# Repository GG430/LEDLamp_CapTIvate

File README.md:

View this project on [CADLAB.io](https://cadlab.io/project/1076). 

# LEDLamp_CapTIvate

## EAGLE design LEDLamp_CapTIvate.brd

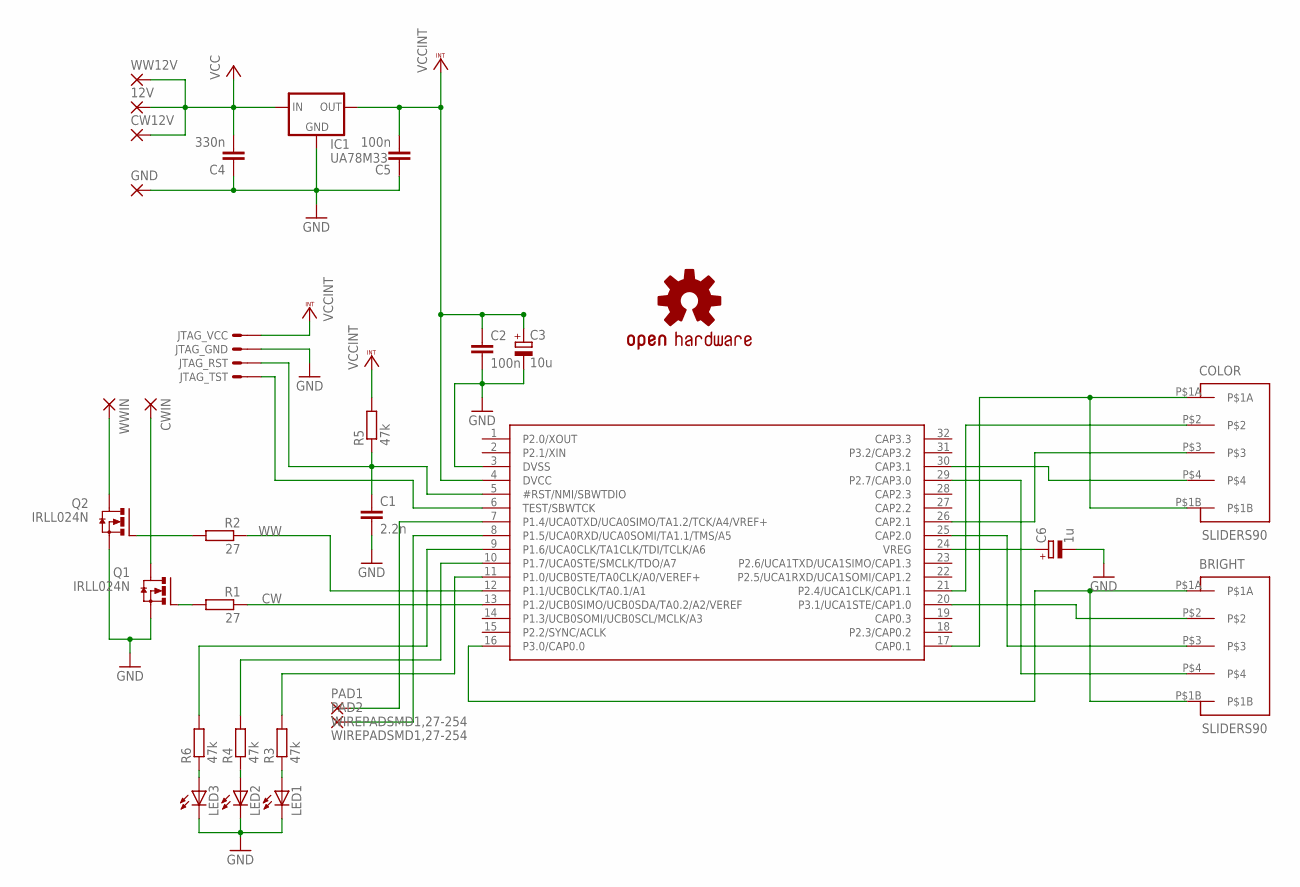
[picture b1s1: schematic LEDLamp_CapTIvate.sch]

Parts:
12V: SMD5; SMD2,54-5,08
BRIGHT: SLIDERS90; SLIDER90
C1: 2.2n; C0805
C2, C5: 100n; C0805
C3: 10u; R/2012-12R
C4: 330n; C0805
C6: 1u; R/2012-12R
COLOR: SLIDERS90; SLIDER90
CW12V: SMD5; SMD2,54-5,08
CWIN: SMD5; SMD2,54-5,08
GND: SMD5; SMD2,54-5,08
IC1: UA78M33; SOT223
JTAG_: MSP430SBWMPE; MPE-374-04
LED1, LED2, LED3: LEDTOPLED-SANTANA; MINI-TOPLED-SANTANA
MSP430FR2633: FR2633; DA32
PAD1, PAD2: WIREPADSMD1,27-254; SMD3X1.5
Q1, Q2: IRLL024N; SOT223
R1, R2: 27; R0805
R3, R4, R5, R6: 47k; R0805
U$2: OSHW_LOGO_SYMM; OSHW_LOGO_MED_SYM
WW12V: SMD5; SMD2,54-5,08
WWIN: SMD5; SMD2,54-5,08

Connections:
CW: MSP430FR2633.13 (P1.2/UCB0SIMO/UCB0SDA/TA0.2/A2/VEREF), R1.1
GND: C1.2, C2.2, C3.-, C4.1, C5.1, C6.-, GND.1, IC1.2 (GND), JTAG_.P$2, LED1.C, LED2.C, LED3.C, MSP430FR2633.3 (DVSS), Q1.3 (S), Q2.3 (S)
unnamed: BRIGHT.P$1A, BRIGHT.P$1B, MSP430FR2633.16 (P3.0/CAP0.0)
unnamed: BRIGHT.P$2, MSP430FR2633.20 (P3.1/UCA1STE/CAP1.0)
unnamed: BRIGHT.P$3, MSP430FR2633.25 (CAP2.0)
unnamed: BRIGHT.P$4, MSP430FR2633.29 (P2.7/CAP3.0)
unnamed: COLOR.P$1A, COLOR.P$1B, MSP430FR2633.17 (CAP0.1)
unnamed: COLOR.P$2, MSP430FR2633.21 (P2.4/UCA1CLK/CAP1.1)
unnamed: COLOR.P$3, MSP430FR2633.26 (CAP2.1)
unnamed: COLOR.P$4, MSP430FR2633.30 (CAP3.1)
unnamed: Q1.1 (G), R1.2
unnamed: Q2.1 (G), R2.2
unnamed: Q2.2 (D), Q2.4 (D), WWIN.1
unnamed: CWIN.1, Q1.2 (D), Q1.4 (D)
unnamed: LED3.A, R6.1
unnamed: LED2.A, R4.1
unnamed: LED1.A, R3.1
unnamed: MSP430FR2633.11 (P1.0/UCB0STE/TA0CLK/A0/VEREF+), R3.2
unnamed: MSP430FR2633.10 (P1.7/UCA0STE/SMCLK/TDO/A7), R4.2
unnamed: MSP430FR2633.9 (P1.6/UCA0CLK/TA1CLK/TDI/TCLK/A6), R6.2
unnamed: C6.+, MSP430FR2633.24 (VREG)
RST: C1.1, JTAG_.P$3, MSP430FR2633.5 (#RST/NMI/SBWTDIO), R5.1
RX: MSP430FR2633.8 (P1.5/UCA0RXD/UCA0SOMI/TA1.1/TMS/A5), PAD2.P$1
TST: JTAG_.P$4, MSP430FR2633.6 (TEST/SBWTCK)
TX: MSP430FR2633.7 (P1.4/UCA0TXD/UCA0SIMO/TA1.2/TCK/A4/VREF+), PAD1.P$1
VCC: 12V.1, C4.2, CW12V.1, IC1.1 (IN), WW12V.1
VCCINT: C2.1, C3.+, C5.2, IC1.3 (OUT), JTAG_.P$1, MSP430FR2633.4 (DVCC), R5.2
WW: MSP430FR2633.12 (P1.1/UCB0CLK/TA0.1/A1), R2.1

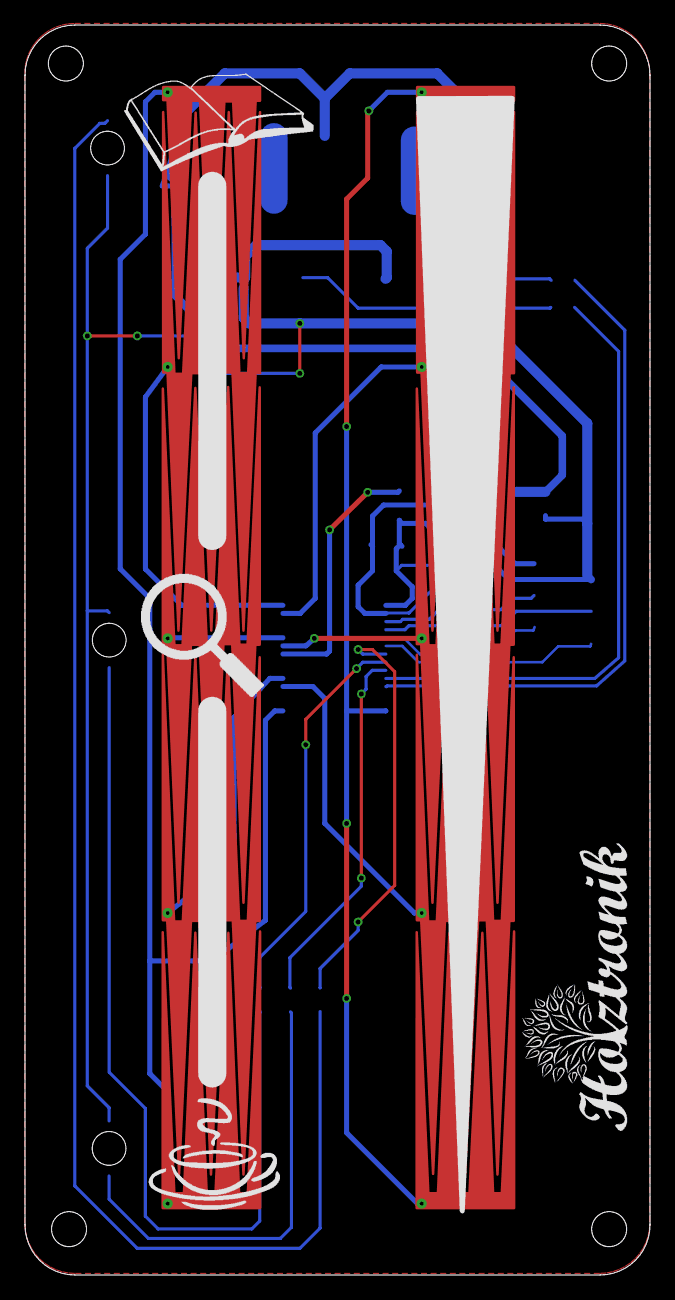
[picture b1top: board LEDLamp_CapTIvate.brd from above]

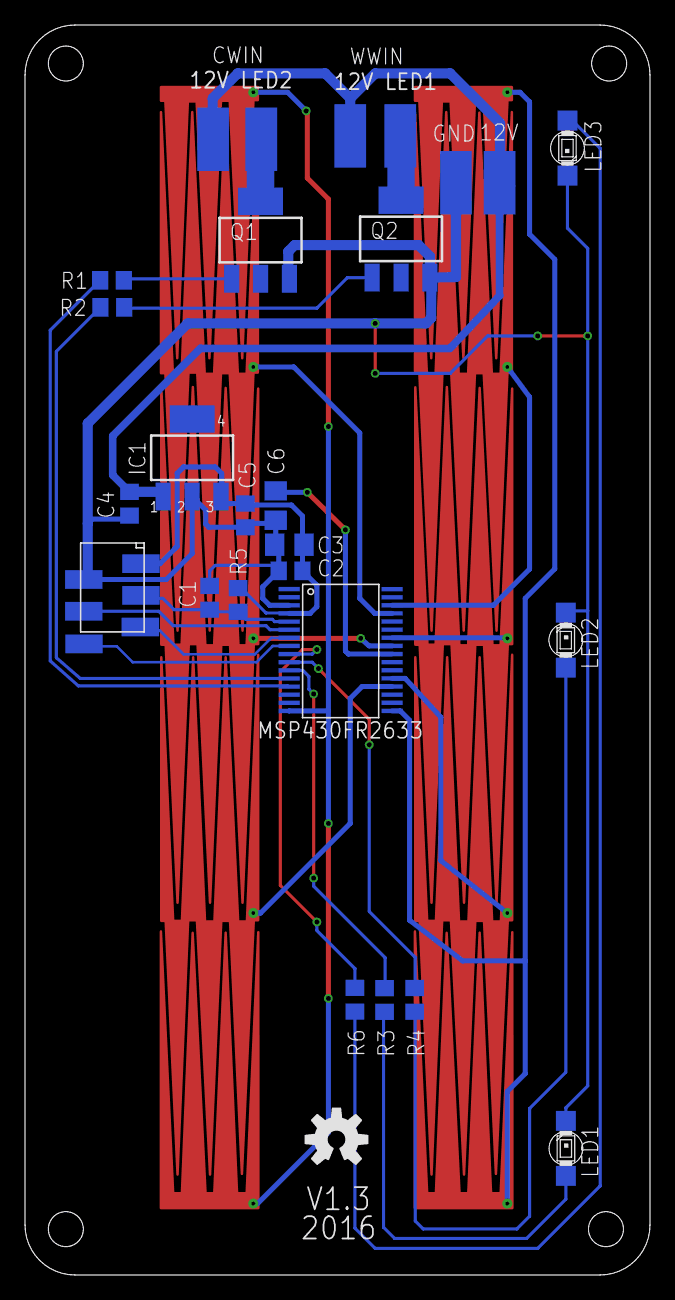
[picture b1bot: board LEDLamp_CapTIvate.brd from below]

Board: 2 copper layers, 50.0 x 100.0 mm, 35 parts (29 on the bottom side), 28 nets.

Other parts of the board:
U$3: HOLZTRONIK5
U$6: BUCH1
U$7: LUPE1
U$8: TASSE1

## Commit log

2018-05-23 V1.0
2018-05-23 V1.1
2018-05-23 V1.2
2018-05-23 V1.3
2018-05-23 Backlink to CADLAB.io has been added.

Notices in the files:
parts and their libraries:
PatternAgents-Logos: License : http://creativecommons.org/licenses/by-sa/3.0
(Creative Commons 3.0)
